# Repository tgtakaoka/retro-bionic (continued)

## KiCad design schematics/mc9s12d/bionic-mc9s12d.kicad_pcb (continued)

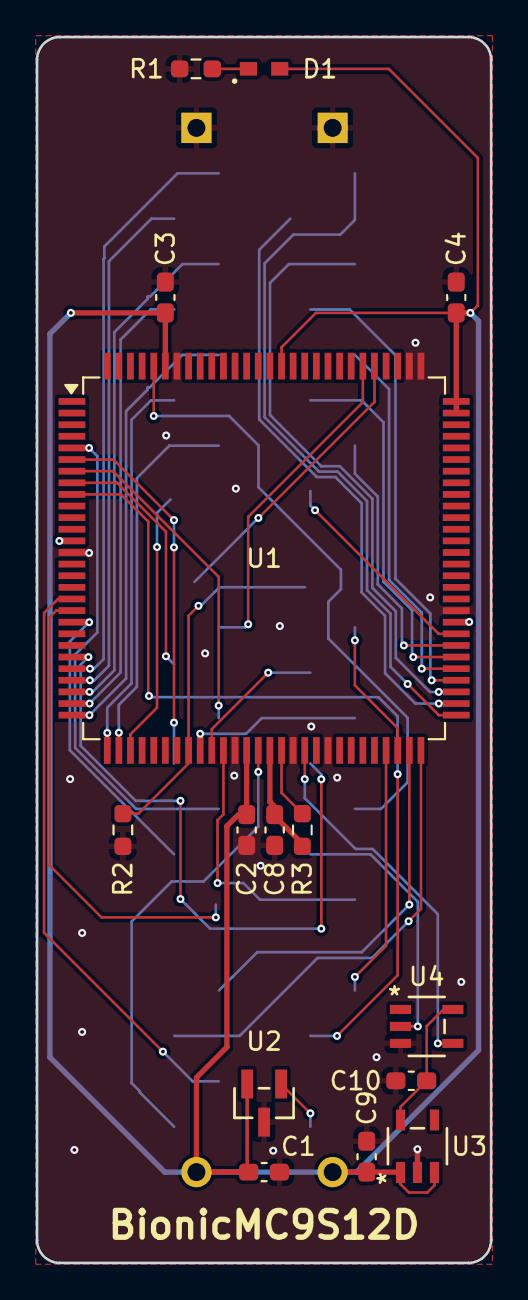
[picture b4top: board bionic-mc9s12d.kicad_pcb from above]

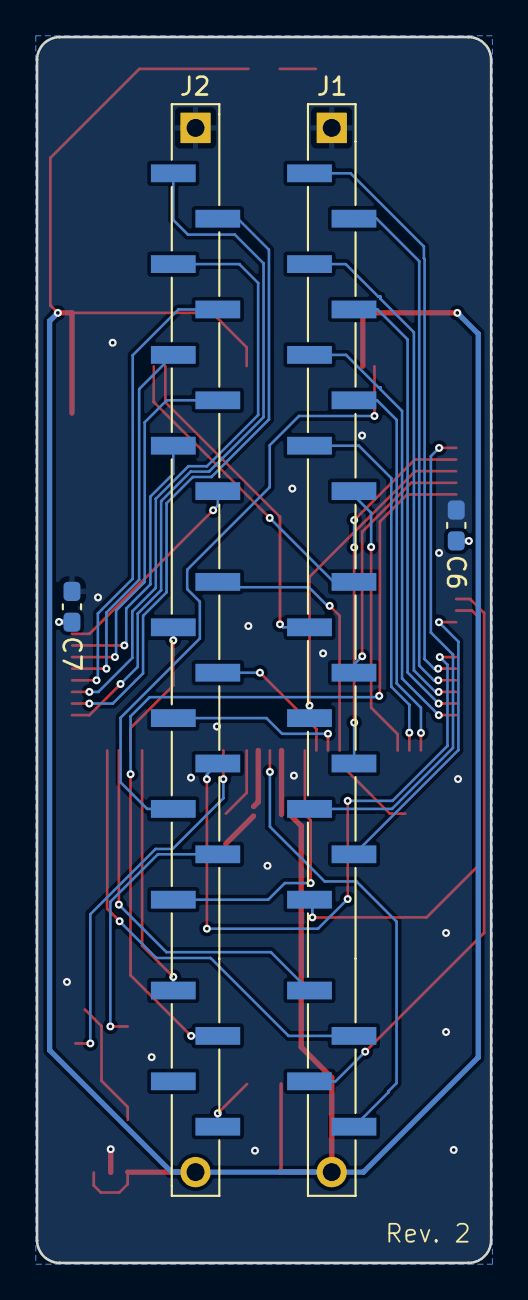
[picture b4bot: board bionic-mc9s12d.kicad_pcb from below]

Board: 2 copper layers, 25.4 x 68.6 mm, 19 parts (4 on the bottom side), 48 nets.

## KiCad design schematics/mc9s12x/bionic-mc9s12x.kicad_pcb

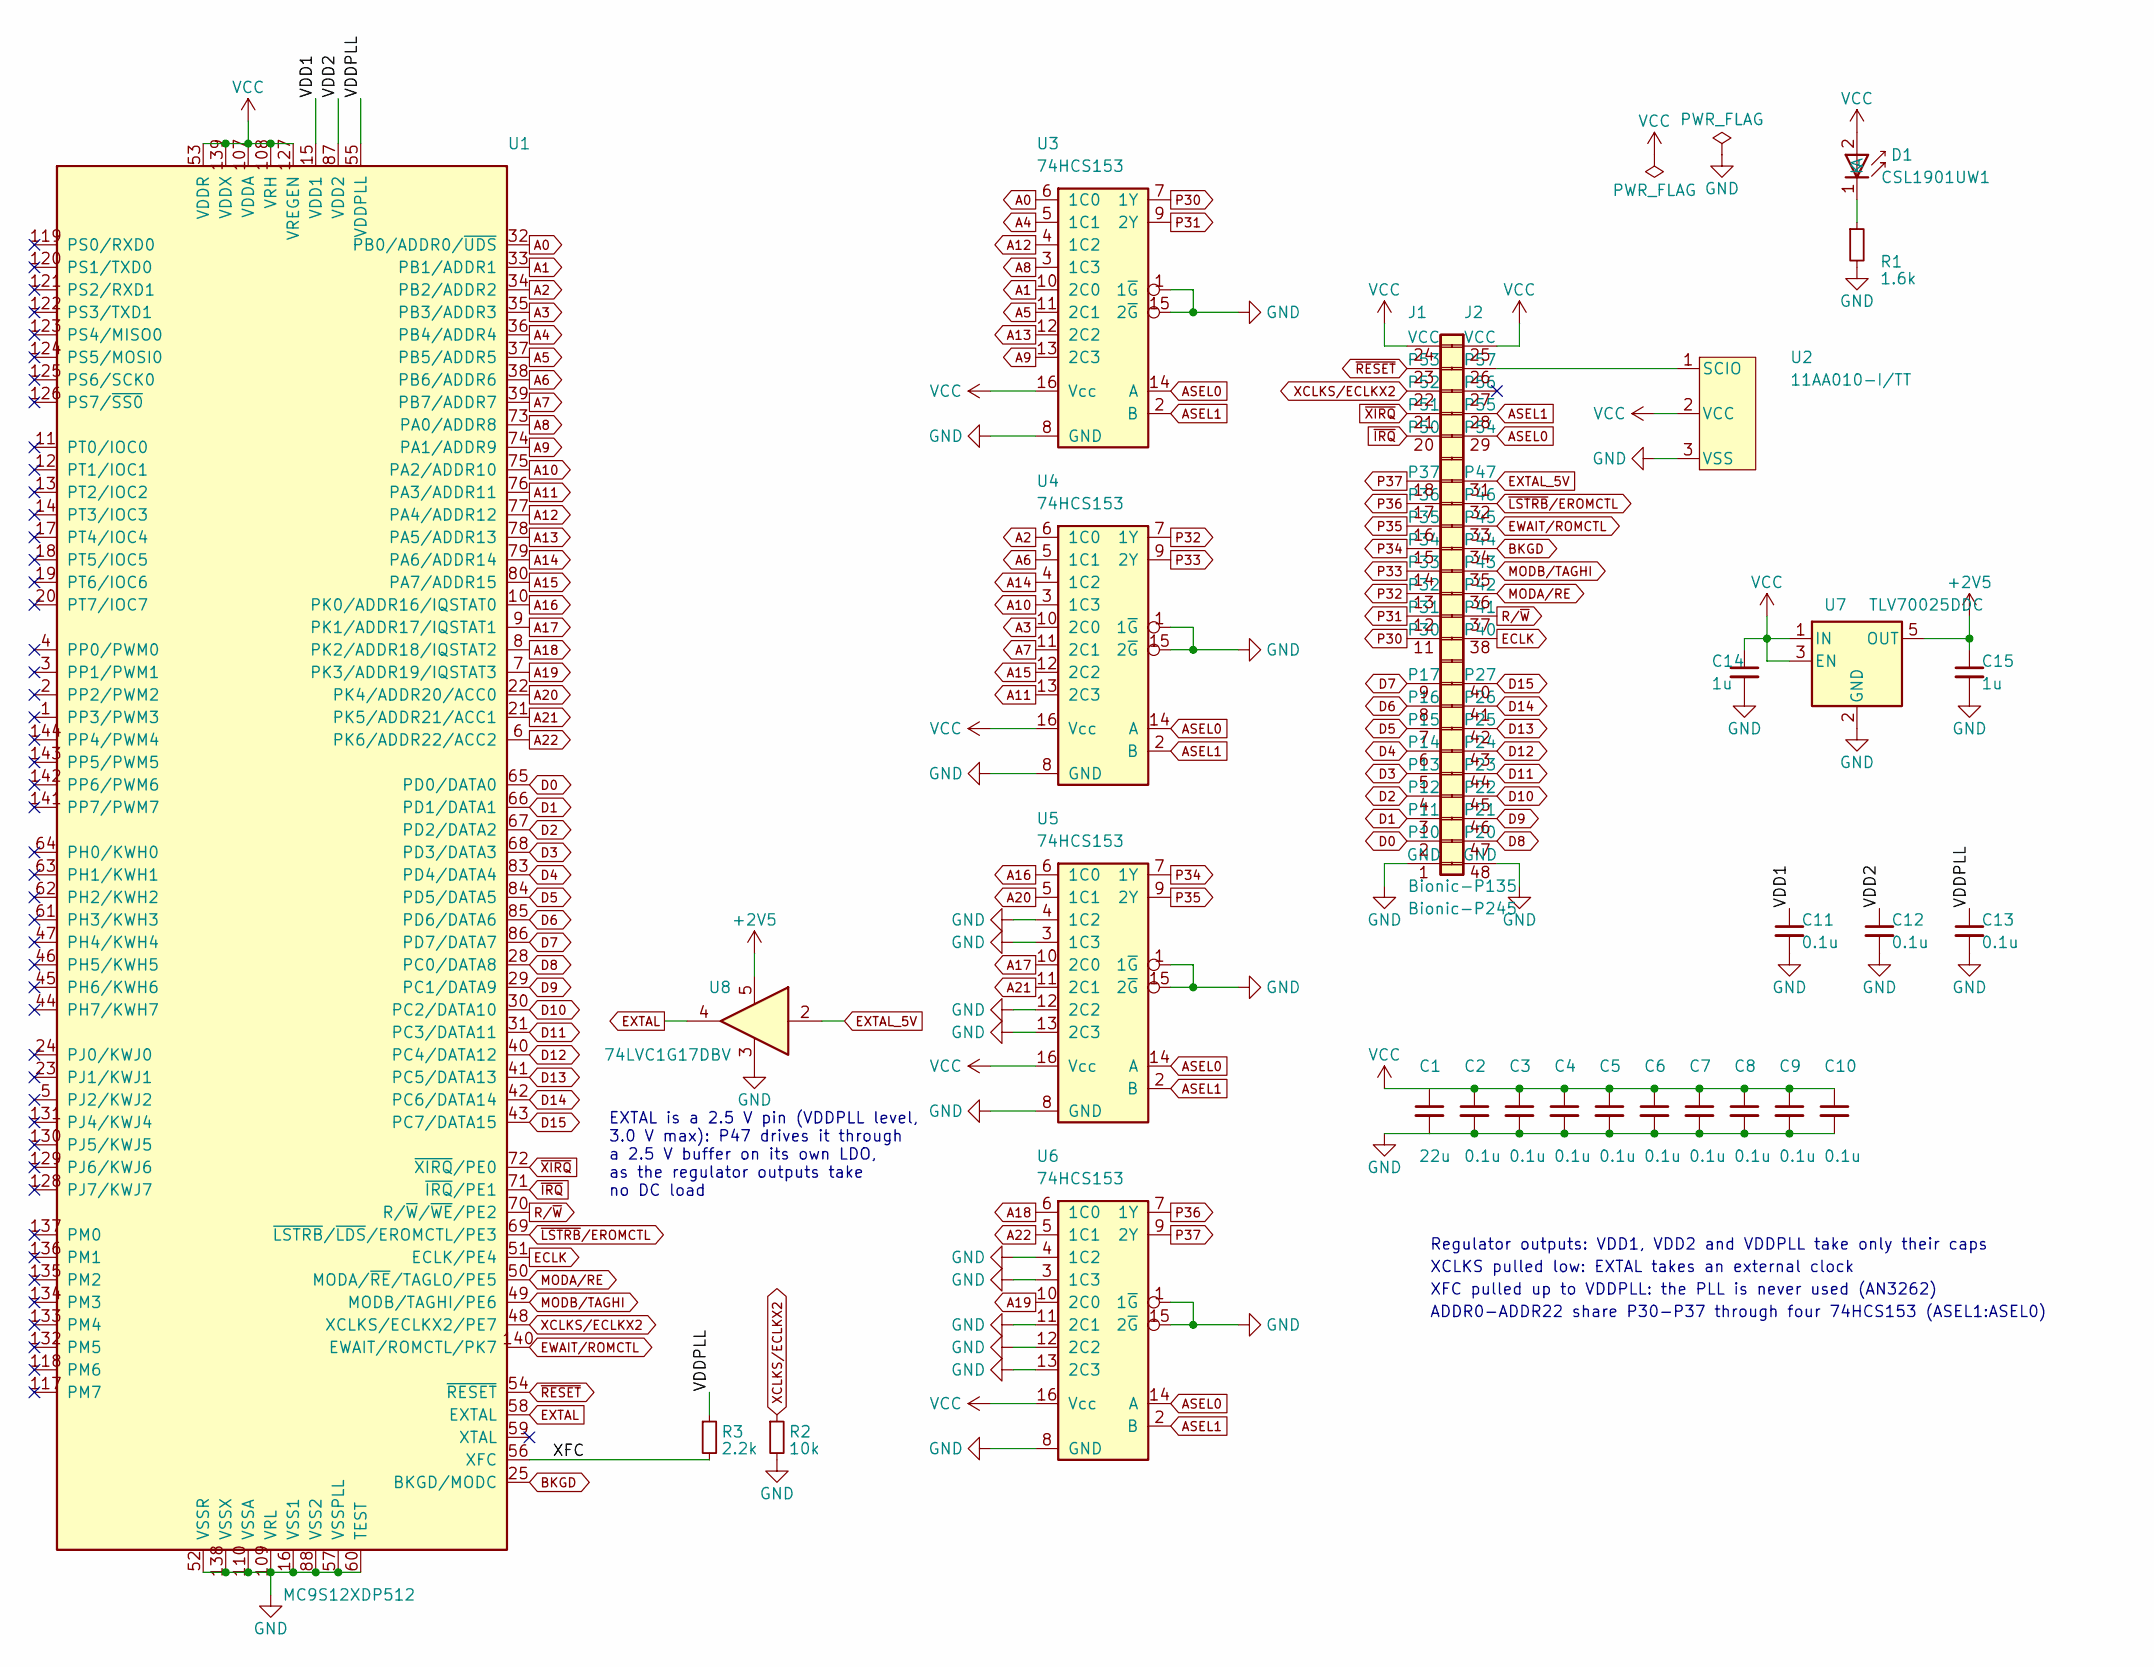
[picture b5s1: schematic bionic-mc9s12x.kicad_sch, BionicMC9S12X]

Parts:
C1: 22u; C_0603_1608Metric_Pad1.08x0.95mm_HandSolder
C2, C3, C4, C5, C6, C7, C8, C9, C10, C11, C12, C13: 0.1u; C_0603_1608Metric_Pad1.08x0.95mm_HandSolder
C14, C15: 1u; C_0603_1608Metric_Pad1.08x0.95mm_HandSolder
D1: CSL1901UW1; LED_CSL1901UW1_ROM-M
J1: Bionic-P135; Bionic-P135_SMT
J2: Bionic-P245; Bionic-P245_SMT
R1: 1.6k; R_0603_1608Metric_Pad0.98x0.95mm_HandSolder
R2: 10k; R_0603_1608Metric_Pad0.98x0.95mm_HandSolder
R3: 2.2k; R_0603_1608Metric_Pad0.98x0.95mm_HandSolder
U1: MC9S12XDP512; LQFP-144_20x20mm_P0.5mm
U2: 11AA010-I/TT; SOT-23_MC_MCH-M
U3, U4, U5, U6: 74HCS153; PW16-M
U7: TLV70025DDC; DBV5-M
U8: 74LVC1G17DBV; DBV5-M

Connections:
+2V5: C15.1, U7.5 (OUT), U8.5 (VCC)
/VDD1: C11.1, U1.15 (VDD1)
/VDD2: C12.1, U1.87 (VDD2)
/VDDPLL: C13.1, R3.1, U1.55 (VDDPLL)
/XFC: R3.2, U1.56 (XFC)
A0: U1.32 (PB0/ADDR0/~UDS), U3.6 (1C0)
A1: U1.33 (PB1/ADDR1), U3.10 (2C0)
A2: U1.34 (PB2/ADDR2), U4.6 (1C0)
A3: U1.35 (PB3/ADDR3), U4.10 (2C0)
A4: U1.36 (PB4/ADDR4), U3.5 (1C1)
A5: U1.37 (PB5/ADDR5), U3.11 (2C1)
A6: U1.38 (PB6/ADDR6), U4.5 (1C1)
A7: U1.39 (PB7/ADDR7), U4.11 (2C1)
A8: U1.73 (PA0/ADDR8), U3.3 (1C3)
A9: U1.74 (PA1/ADDR9), U3.13 (2C3)
A10: U1.75 (PA2/ADDR10), U4.3 (1C3)
A11: U1.76 (PA3/ADDR11), U4.13 (2C3)
A12: U1.77 (PA4/ADDR12), U3.4 (1C2)
A13: U1.78 (PA5/ADDR13), U3.12 (2C2)
A14: U1.79 (PA6/ADDR14), U4.4 (1C2)
A15: U1.80 (PA7/ADDR15), U4.12 (2C2)
A16: U1.10 (PK0/ADDR16/IQSTAT0), U5.6 (1C0)
A17: U1.9 (PK1/ADDR17/IQSTAT1), U5.10 (2C0)
A18: U1.8 (PK2/ADDR18/IQSTAT2), U6.6 (1C0)
A19: U1.7 (PK3/ADDR19/IQSTAT3), U6.10 (2C0)
A20: U1.22 (PK4/ADDR20/ACC0), U5.5 (1C1)
A21: U1.21 (PK5/ADDR21/ACC1), U5.11 (2C1)
A22: U1.6 (PK6/ADDR22/ACC2), U6.5 (1C1)
ASEL0: J2.29 (P54), U3.14 (A), U4.14 (A), U5.14 (A), U6.14 (A)
ASEL1: J2.28 (P55), U3.2 (B), U4.2 (B), U5.2 (B), U6.2 (B)
BKGD: J2.34 (P44), U1.25 (BKGD/MODC)
D0: J1.2 (P10), U1.65 (PD0/DATA0)
D1: J1.3 (P11), U1.66 (PD1/DATA1)
D2: J1.4 (P12), U1.67 (PD2/DATA2)
D3: J1.5 (P13), U1.68 (PD3/DATA3)
D4: J1.6 (P14), U1.83 (PD4/DATA4)
D5: J1.7 (P15), U1.84 (PD5/DATA5)
D6: J1.8 (P16), U1.85 (PD6/DATA6)
D7: J1.9 (P17), U1.86 (PD7/DATA7)
D8: J2.47 (P20), U1.28 (PC0/DATA8)
D9: J2.46 (P21), U1.29 (PC1/DATA9)
D10: J2.45 (P22), U1.30 (PC2/DATA10)
D11: J2.44 (P23), U1.31 (PC3/DATA11)
D12: J2.43 (P24), U1.40 (PC4/DATA12)
D13: J2.42 (P25), U1.41 (PC5/DATA13)
D14: J2.41 (P26), U1.42 (PC6/DATA14)
D15: J2.40 (P27), U1.43 (PC7/DATA15)
ECLK: J2.38 (P40), U1.51 (ECLK/PE4)
EWAIT/ROMCTL: J2.33 (P45), U1.140 (EWAIT/ROMCTL/PK7)
EXTAL: U1.58 (EXTAL), U8.4 (Y)
EXTAL_5V: J2.31 (P47), U8.2 (A)
GND: C1.2, C2.2, C3.2, C4.2, C5.2, C6.2, C7.2, C8.2, C9.2, C10.2, C11.2, C12.2, C13.2, C14.2, C15.2, J1.1 (GND), J2.48 (GND), R1.2, R2.2, U1.16 (VSS1), U1.27 (VSSX), U1.52 (VSSR), U1.57 (VSSPLL), U1.60 (TEST), U1.81 (VSSR), U1.88 (VSS2), U1.109 (VRL), U1.110 (VSSA), U1.138 (VSSX), U2.3 (VSS), U3.1 (1~G), U3.8 (GND), U3.15 (2~G), U4.1 (1~G), U4.8 (GND), U4.15 (2~G), U5.1 (1~G), U5.3 (1C3), U5.4 (1C2), U5.8 (GND), U5.12 (2C2), U5.13 (2C3), U5.15 (2~G), U6.1 (1~G), U6.3 (1C3), U6.4 (1C2), U6.8 (GND), U6.11 (2C1), U6.12 (2C2), U6.13 (2C3), U6.15 (2~G), U7.2 (GND), U8.3 (GND)
MODA/RE: J2.36 (P42), U1.50 (MODA/~RE/TAGLO/PE5)
MODB/TAGHI: J2.35 (P43), U1.49 (MODB/TAGHI/PE6)
unnamed: D1.1 (K), R1.1
unnamed: J2.26 (P57), U2.1 (SCIO)
P30: J1.11 (P30), U3.7 (1Y)
P31: J1.12 (P31), U3.9 (2Y)
P32: J1.13 (P32), U4.7 (1Y)
P33: J1.14 (P33), U4.9 (2Y)
P34: J1.15 (P34), U5.7 (1Y)
P35: J1.16 (P35), U5.9 (2Y)
P36: J1.17 (P36), U6.7 (1Y)
P37: J1.18 (P37), U6.9 (2Y)
R/~W: J2.37 (P41), U1.70 (R/~W/~WE/PE2)
VCC: C1.1, C2.1, C3.1, C4.1, C5.1, C6.1, C7.1, C8.1, C9.1, C10.1, C14.1, D1.2 (A), J1.24 (VCC), J2.25 (VCC), U1.26 (VDDX), U1.53 (VDDR), U1.82 (VDDR), U1.107 (VDDA), U1.108 (VRH), U1.127 (VREGEN), U1.139 (VDDX), U2.2 (VCC), U3.16 (Vcc), U4.16 (Vcc), U5.16 (Vcc), U6.16 (Vcc), U7.1 (IN), U7.3 (EN)
XCLKS/ECLKX2: J1.22 (P52), R2.1, U1.48 (XCLKS/ECLKX2/PE7)
~IRQ: J1.20 (P50), U1.71 (~IRQ/PE1)
~LSTRB/EROMCTL: J2.32 (P46), U1.69 (~LSTRB/~LDS/EROMCTL/PE3)
~RESET: J1.23 (P53), U1.54 (~RESET)
~XIRQ: J1.21 (P51), U1.72 (~XIRQ/PE0)

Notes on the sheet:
XCLKS pulled low: EXTAL takes an external clock
ADDR0-ADDR22 share P30-P37 through four 74HCS153 (ASEL1:ASEL0)
XFC pulled up to VDDPLL: the PLL is never used (AN3262)
EXTAL is a 2.5 V pin (VDDPLL level, 3.0 V max): P47 drives it through a 2.5 V buffer on its own LDO, as the regulator outputs take no DC load
Regulator outputs: VDD1, VDD2 and VDDPLL take only their caps

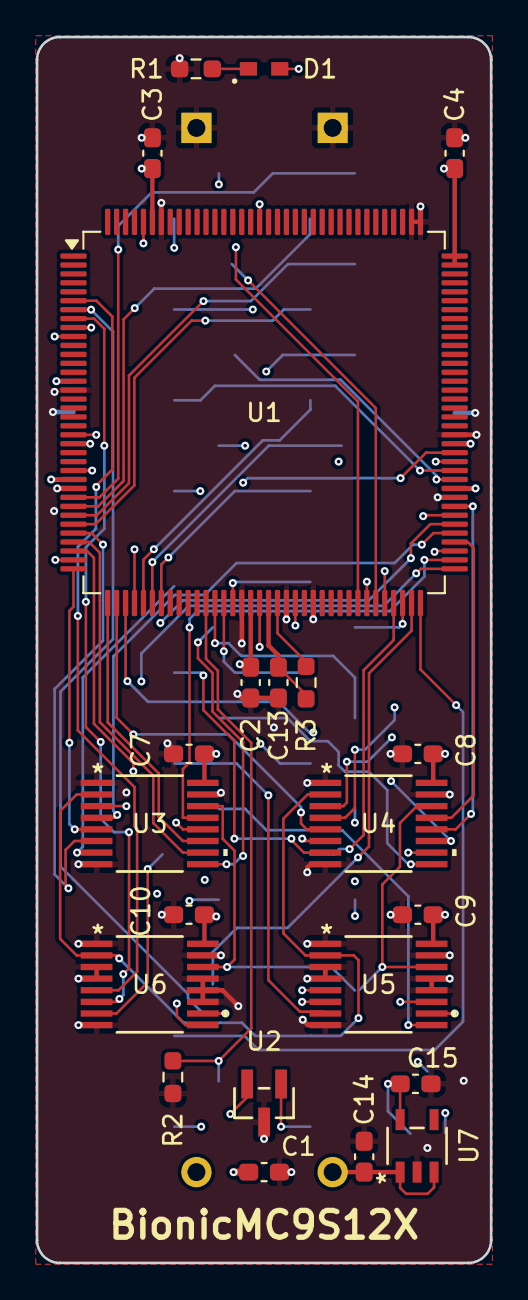
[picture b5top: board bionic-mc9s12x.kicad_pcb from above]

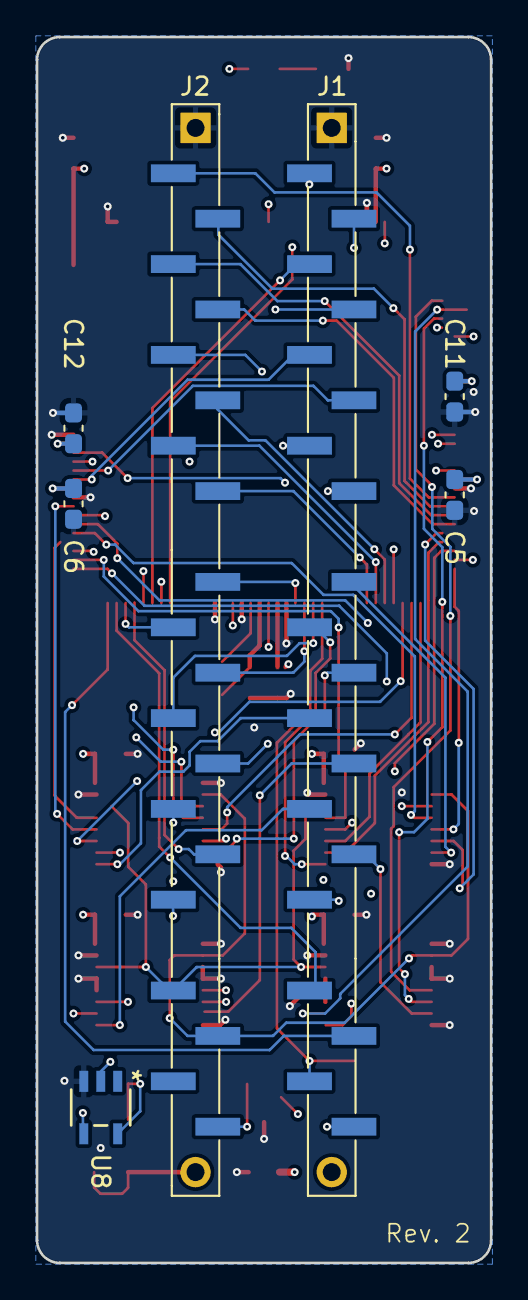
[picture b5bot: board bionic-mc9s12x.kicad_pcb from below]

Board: 4 copper layers, 25.4 x 68.6 mm, 29 parts (7 on the bottom side), 71 nets.

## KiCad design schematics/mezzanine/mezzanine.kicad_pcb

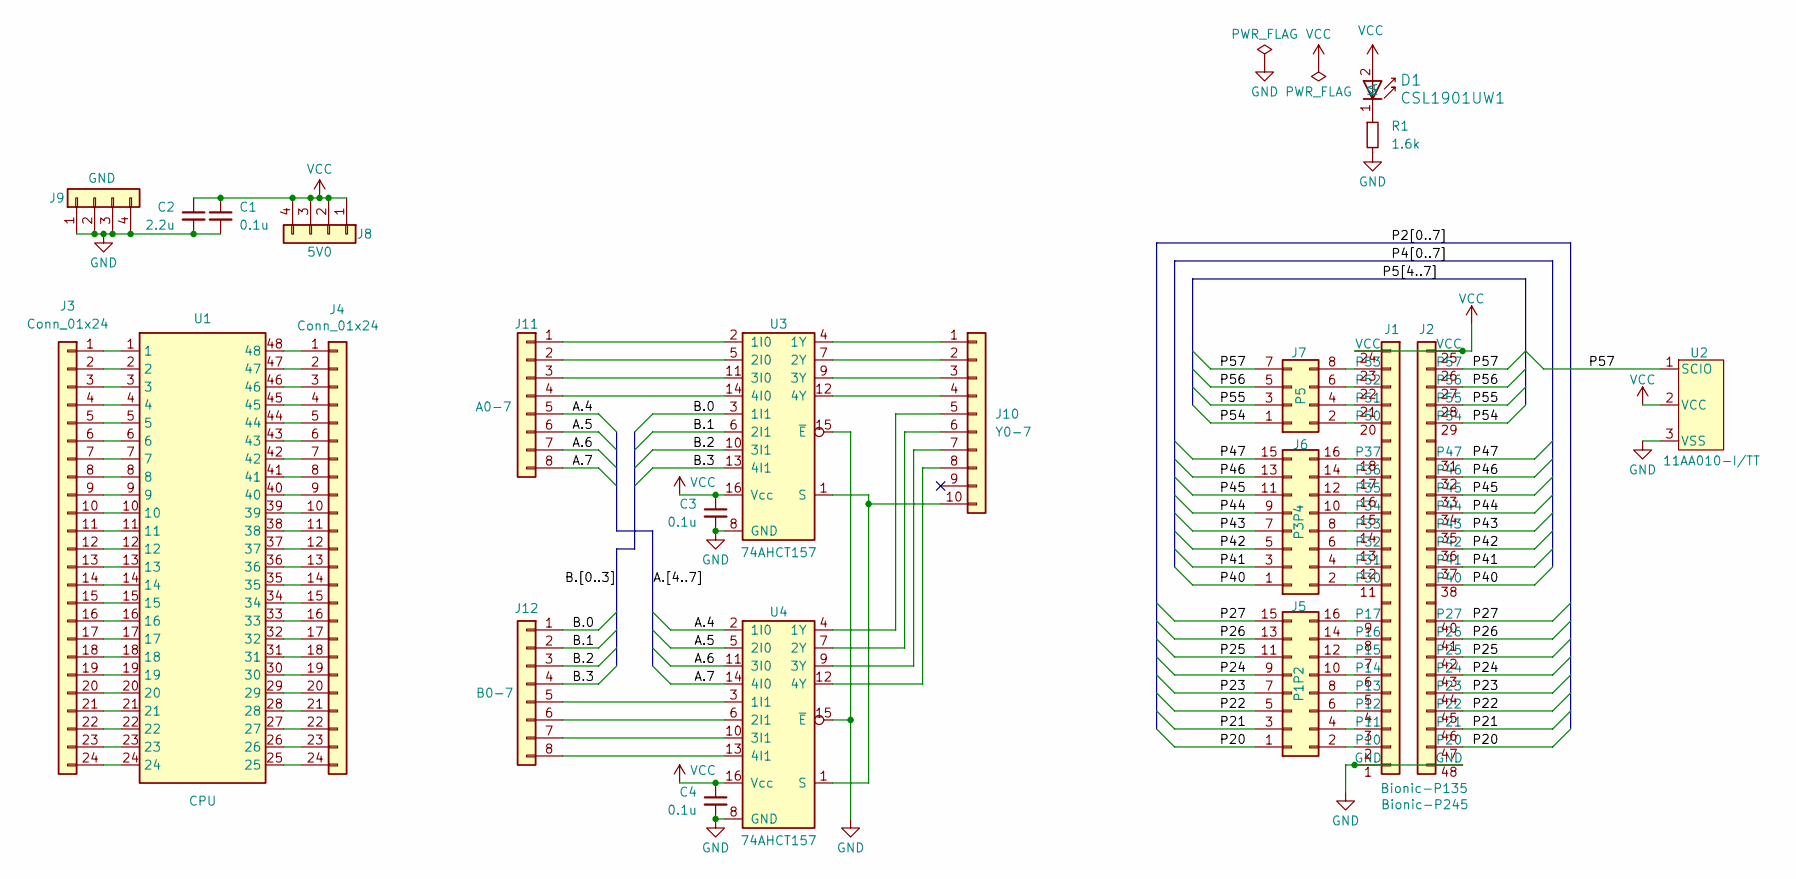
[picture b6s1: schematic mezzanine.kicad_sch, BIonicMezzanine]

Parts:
C1, C3, C4: 0.1u; C_0603_1608Metric_Pad1.08x0.95mm_HandSolder
C2: 2.2u; C_0603_1608Metric_Pad1.08x0.95mm_HandSolder
D1: CSL1901UW1; LED_CSL1901UW1_ROM-M
J1: Bionic-P135; Bionic-P135_THT
J2: Bionic-P245; Bionic-P245_THT
J3, J4: Conn_01x24; PinSocket_1x24_P2.54mm_Vertical
J5: P1P2; PinSocket_2x08_P2.54mm_Vertical
J6: P3P4; PinSocket_2x08_P2.54mm_Vertical
J7: P5; PinSocket_2x04_P2.54mm_Vertical
J8: 5V0; PinSocket_1x04_P2.54mm_Vertical
J9: GND; PinSocket_1x04_P2.54mm_Vertical
J10: Y0-7; PinSocket_1x10_P2.54mm_Vertical
J11: A0-7; PinSocket_1x08_P2.54mm_Vertical
J12: B0-7; PinSocket_1x08_P2.54mm_Vertical
R1: 1.6k; R_0603_1608Metric_Pad0.98x0.95mm_HandSolder
U1: CPU; Aries_ZIF_socket_DIP-48-pin
U2: 11AA010-I/TT; SOT-23_MC_MCH-M
U3, U4: 74AHCT157; PW16-M

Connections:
/A.4: J11.5, U4.2 (1I0)
/A.5: J11.6, U4.5 (2I0)
/A.6: J11.7, U4.11 (3I0)
/A.7: J11.8, U4.14 (4I0)
/B.0: J12.1, U3.3 (1I1)
/B.1: J12.2, U3.6 (2I1)
/B.2: J12.3, U3.10 (3I1)
/B.3: J12.4, U3.13 (4I1)
/P20: J2.47 (P20), J5.1
/P21: J2.46 (P21), J5.3
/P22: J2.45 (P22), J5.5
/P23: J2.44 (P23), J5.7
/P24: J2.43 (P24), J5.9
/P25: J2.42 (P25), J5.11
/P26: J2.41 (P26), J5.13
/P27: J2.40 (P27), J5.15
/P40: J2.38 (P40), J6.1
/P41: J2.37 (P41), J6.3
/P42: J2.36 (P42), J6.5
/P43: J2.35 (P43), J6.7
/P44: J2.34 (P44), J6.9
/P45: J2.33 (P45), J6.11
/P46: J2.32 (P46), J6.13
/P47: J2.31 (P47), J6.15
/P54: J2.29 (P54), J7.1
/P55: J2.28 (P55), J7.3
/P56: J2.27 (P56), J7.5
/P57: J2.26 (P57), J7.7, U2.1 (SCIO)
GND: C1.2, C2.2, C3.2, C4.2, J1.1 (GND), J2.48 (GND), J9.1, J9.2, J9.3, J9.4, R1.2, U2.3 (VSS), U3.8 (GND), U3.15 (~E), U4.8 (GND), U4.15 (~E)
unnamed: D1.1 (K), R1.1
unnamed: J1.2 (P10), J5.2
unnamed: J1.3 (P11), J5.4
unnamed: J1.4 (P12), J5.6
unnamed: J1.5 (P13), J5.8
unnamed: J1.6 (P14), J5.10
unnamed: J1.7 (P15), J5.12
unnamed: J1.8 (P16), J5.14
unnamed: J1.9 (P17), J5.16
unnamed: J1.11 (P30), J6.2
unnamed: J1.12 (P31), J6.4
unnamed: J1.13 (P32), J6.6
unnamed: J1.14 (P33), J6.8
unnamed: J1.15 (P34), J6.10
unnamed: J1.16 (P35), J6.12
unnamed: J1.17 (P36), J6.14
unnamed: J1.18 (P37), J6.16
unnamed: J1.20 (P50), J7.2
unnamed: J1.21 (P51), J7.4
unnamed: J1.22 (P52), J7.6
unnamed: J1.23 (P53), J7.8
unnamed: J3.1, U1.1
unnamed: J3.2, U1.2
unnamed: J3.3, U1.3
unnamed: J3.4, U1.4
unnamed: J3.5, U1.5
unnamed: J3.6, U1.6
unnamed: J3.7, U1.7
unnamed: J3.8, U1.8
unnamed: J3.9, U1.9
unnamed: J3.10, U1.10
unnamed: J3.11, U1.11
unnamed: J3.12, U1.12
unnamed: J3.13, U1.13
unnamed: J3.14, U1.14
unnamed: J3.15, U1.15
unnamed: J3.16, U1.16
unnamed: J3.17, U1.17
unnamed: J3.18, U1.18
unnamed: J3.19, U1.19
unnamed: J3.20, U1.20
unnamed: J3.21, U1.21
unnamed: J3.22, U1.22
unnamed: J3.23, U1.23
unnamed: J3.24, U1.24
unnamed: J4.1, U1.48
unnamed: J4.2, U1.47
unnamed: J4.3, U1.46
unnamed: J4.4, U1.45
unnamed: J4.5, U1.44
unnamed: J4.6, U1.43
unnamed: J4.7, U1.42
unnamed: J4.8, U1.41
unnamed: J4.9, U1.40
unnamed: J4.10, U1.39
unnamed: J4.11, U1.38
unnamed: J4.12, U1.37
unnamed: J4.13, U1.36
unnamed: J4.14, U1.35
unnamed: J4.15, U1.34
unnamed: J4.16, U1.33
unnamed: J4.17, U1.32
unnamed: J4.18, U1.31
unnamed: J4.19, U1.30
unnamed: J4.20, U1.29
unnamed: J4.21, U1.28
unnamed: J4.22, U1.27
unnamed: J4.23, U1.26
unnamed: J4.24, U1.25
unnamed: J10.1, U3.4 (1Y)
unnamed: J10.2, U3.7 (2Y)
unnamed: J10.3, U3.9 (3Y)
unnamed: J10.4, U3.12 (4Y)
unnamed: J10.5, U4.4 (1Y)
unnamed: J10.6, U4.7 (2Y)
unnamed: J10.7, U4.9 (3Y)
unnamed: J10.8, U4.12 (4Y)
unnamed: J10.10, U3.1 (S), U4.1 (S)
unnamed: J11.1, U3.2 (1I0)
unnamed: J11.2, U3.5 (2I0)
unnamed: J11.3, U3.11 (3I0)
unnamed: J11.4, U3.14 (4I0)
unnamed: J12.5, U4.3 (1I1)
unnamed: J12.6, U4.6 (2I1)
unnamed: J12.7, U4.10 (3I1)
unnamed: J12.8, U4.13 (4I1)
VCC: C1.1, C2.1, C3.1, C4.1, D1.2 (A), J1.24 (VCC), J2.25 (VCC), J8.1, J8.2, J8.3, J8.4, U2.2 (VCC), U3.16 (Vcc), U4.16 (Vcc)

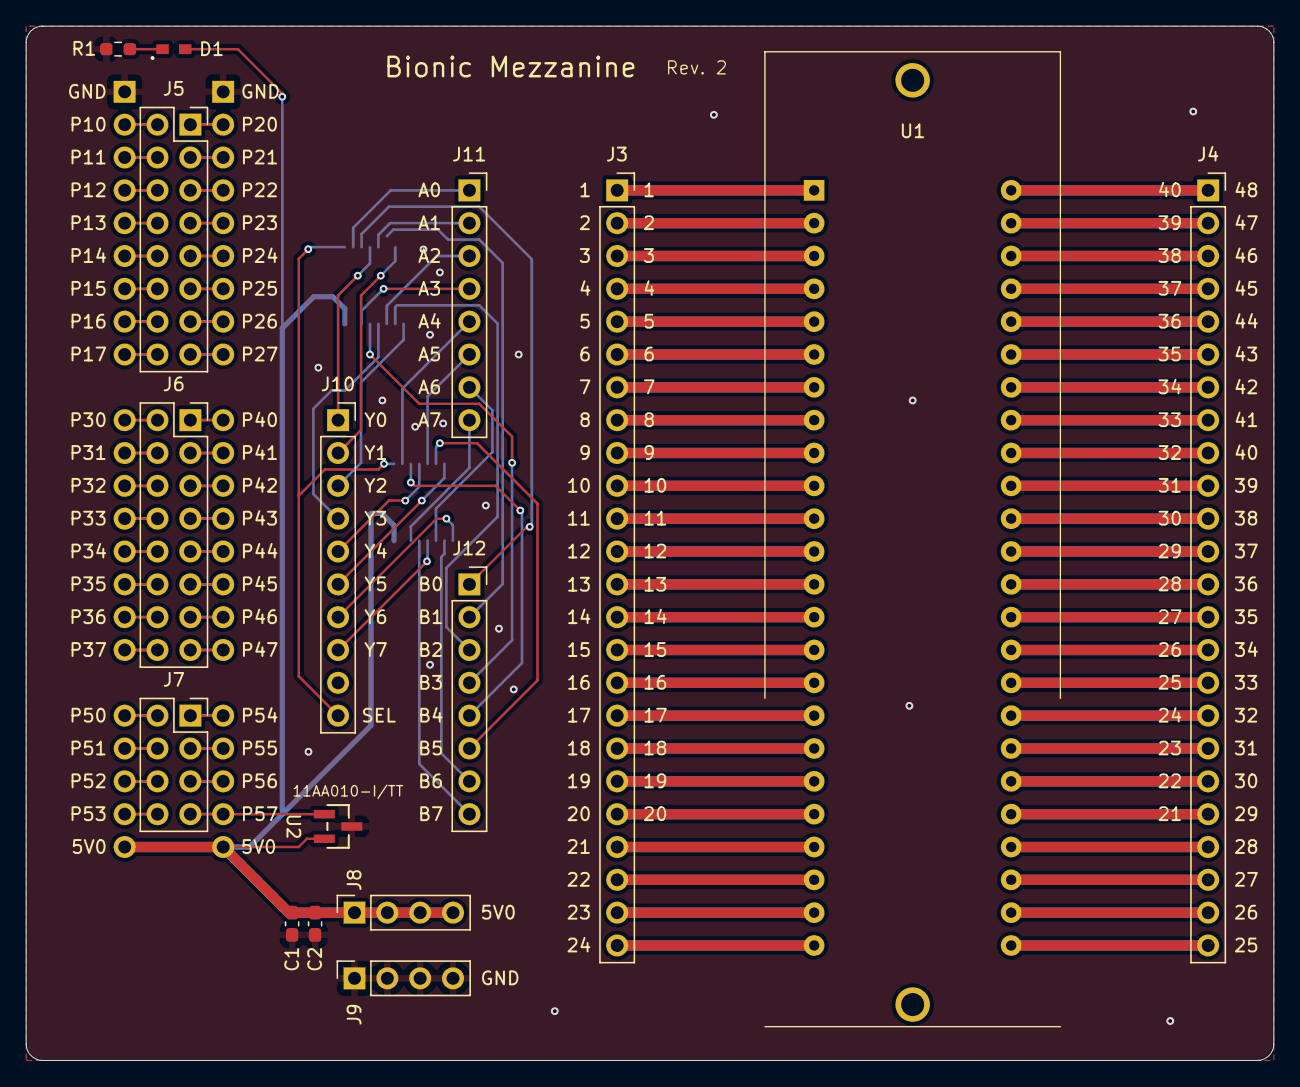
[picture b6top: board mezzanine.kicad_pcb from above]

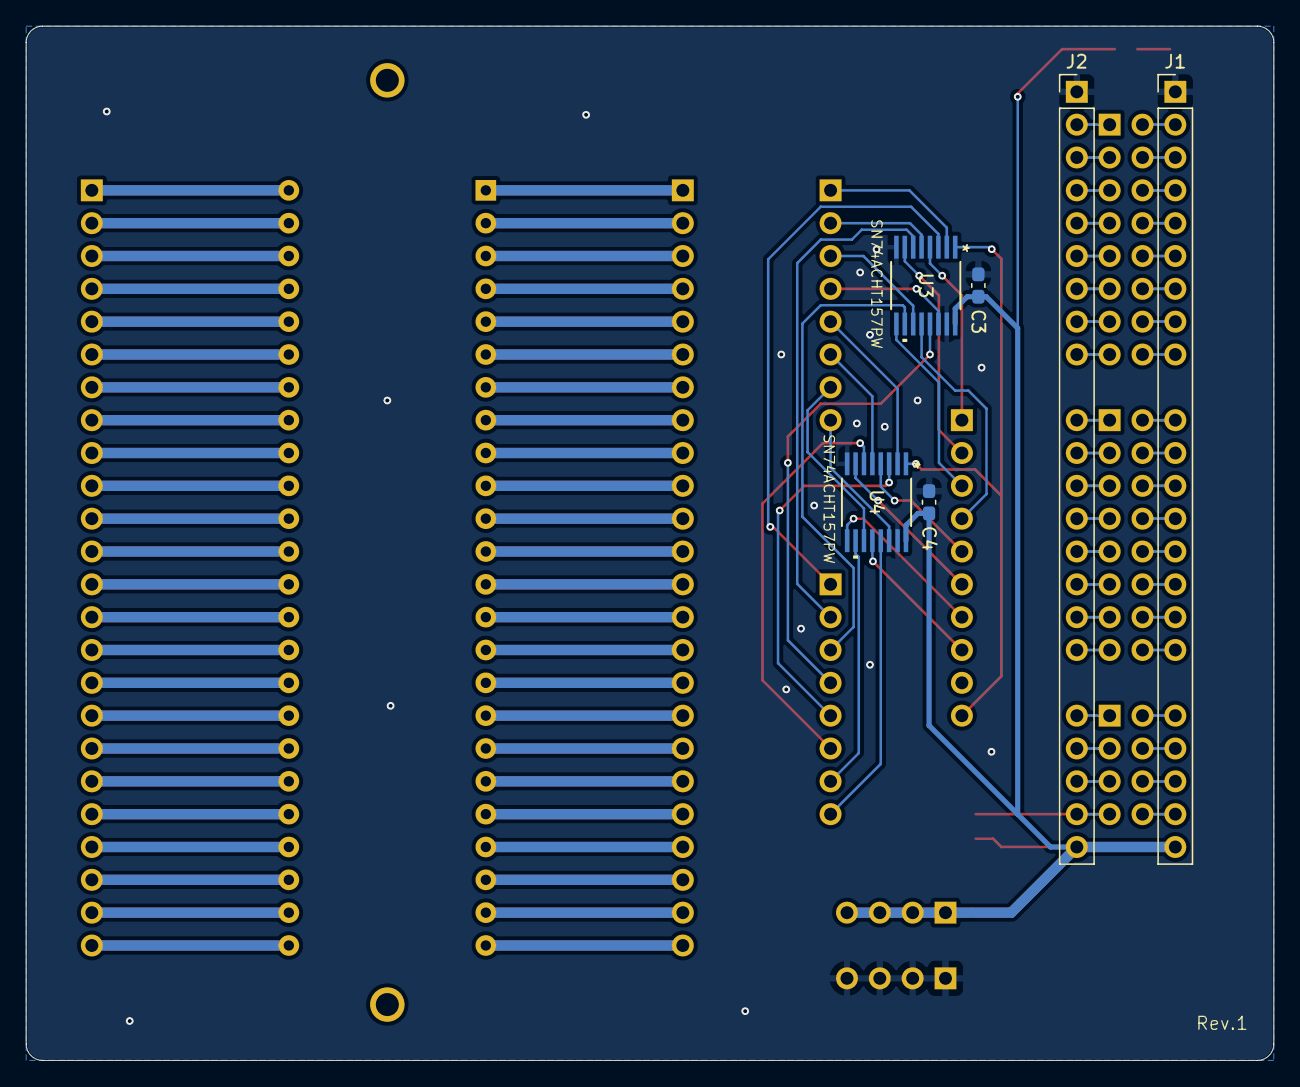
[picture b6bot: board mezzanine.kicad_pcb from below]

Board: 2 copper layers, 96.5 x 80.0 mm, 22 parts (6 on the bottom side), 116 nets.

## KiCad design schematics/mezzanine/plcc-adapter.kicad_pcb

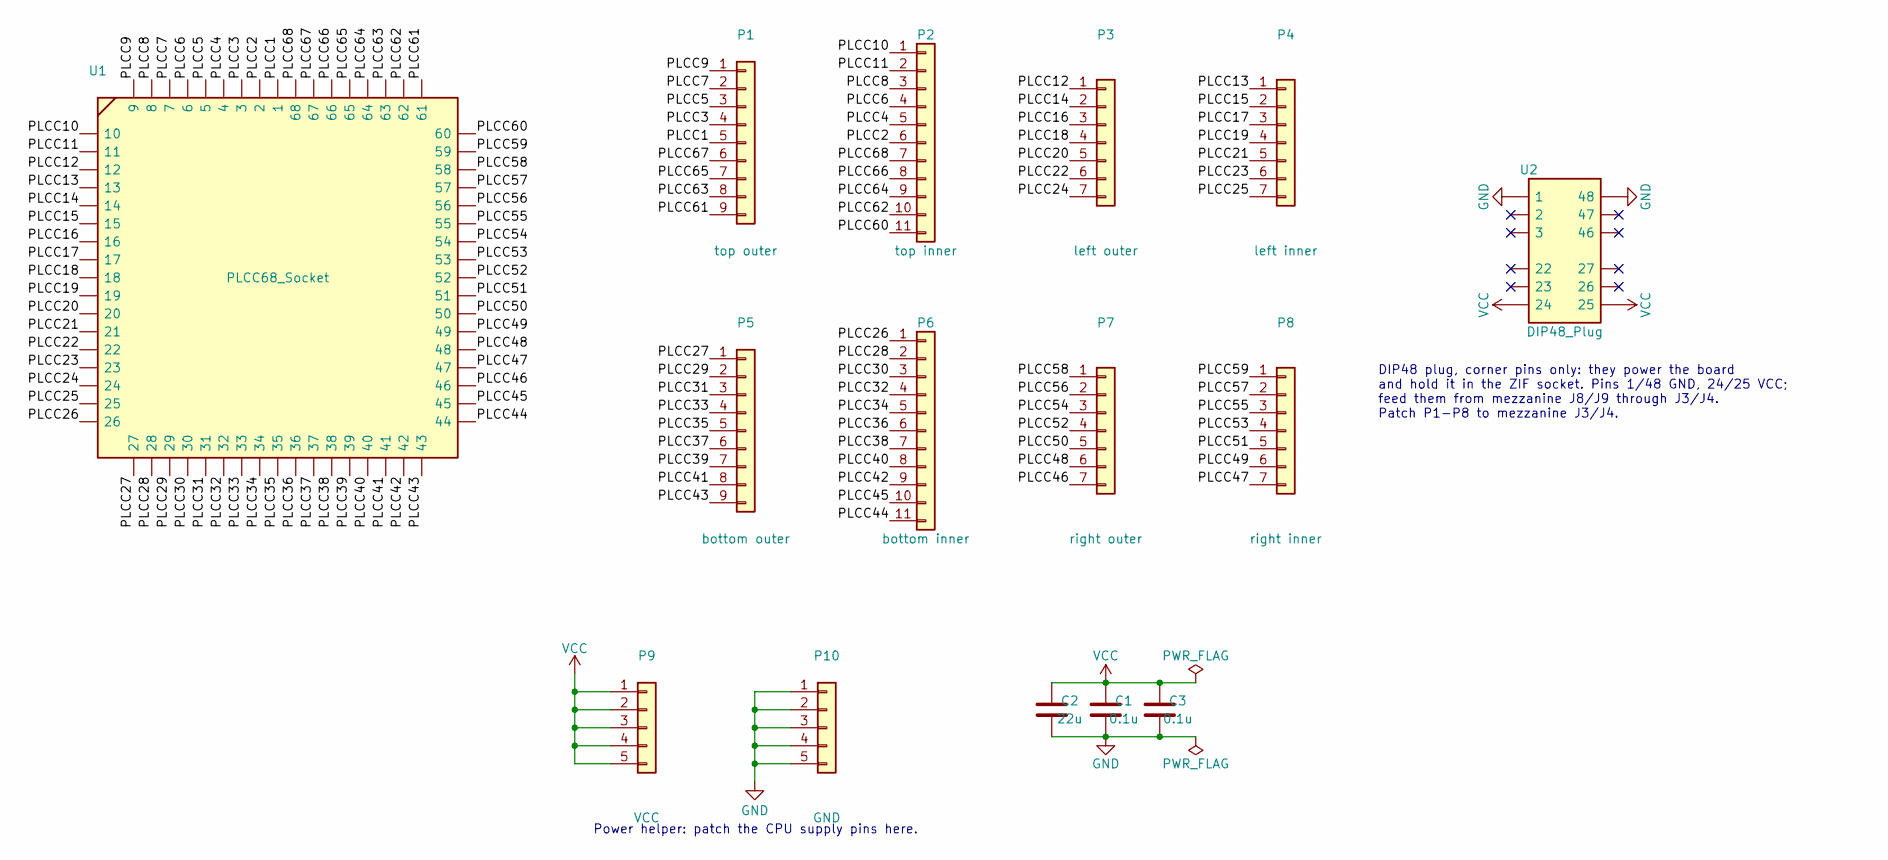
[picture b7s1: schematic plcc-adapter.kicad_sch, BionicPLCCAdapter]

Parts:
C1, C3: 0.1u; C_0603_1608Metric_Pad1.08x0.95mm_HandSolder
C2: 22u; C_0603_1608Metric_Pad1.08x0.95mm_HandSolder
P1: top outer; PinSocket_1x09_P2.54mm_Vertical_Oval
P2: top inner; PinSocket_1x11_P2.54mm_Vertical_Oval
P3: left outer; PinSocket_1x07_P2.54mm_Vertical_Oval
P4: left inner; PinSocket_1x07_P2.54mm_Vertical_Oval
P5: bottom outer; PinSocket_1x09_P2.54mm_Vertical_Oval
P6: bottom inner; PinSocket_1x11_P2.54mm_Vertical_Oval
P7: right outer; PinSocket_1x07_P2.54mm_Vertical_Oval
P8: right inner; PinSocket_1x07_P2.54mm_Vertical_Oval
P9: VCC; PinSocket_1x05_P2.54mm_Vertical_Oval
P10: GND; PinSocket_1x05_P2.54mm_Vertical_Oval
U1: PLCC68_Socket; PLCC-68_THT-Socket_Akizuki
U2: DIP48_Plug

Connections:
/PLCC1: P1.5, U1.1
/PLCC2: P2.6, U1.2
/PLCC3: P1.4, U1.3
/PLCC4: P2.5, U1.4
/PLCC5: P1.3, U1.5
/PLCC6: P2.4, U1.6
/PLCC7: P1.2, U1.7
/PLCC8: P2.3, U1.8
/PLCC9: P1.1, U1.9
/PLCC10: P2.1, U1.10
/PLCC11: P2.2, U1.11
/PLCC12: P3.1, U1.12
/PLCC13: P4.1, U1.13
/PLCC14: P3.2, U1.14
/PLCC15: P4.2, U1.15
/PLCC16: P3.3, U1.16
/PLCC17: P4.3, U1.17
/PLCC18: P3.4, U1.18
/PLCC19: P4.4, U1.19
/PLCC20: P3.5, U1.20
/PLCC21: P4.5, U1.21
/PLCC22: P3.6, U1.22
/PLCC23: P4.6, U1.23
/PLCC24: P3.7, U1.24
/PLCC25: P4.7, U1.25
/PLCC26: P6.1, U1.26
/PLCC27: P5.1, U1.27
/PLCC28: P6.2, U1.28
/PLCC29: P5.2, U1.29
/PLCC30: P6.3, U1.30
/PLCC31: P5.3, U1.31
/PLCC32: P6.4, U1.32
/PLCC33: P5.4, U1.33
/PLCC34: P6.5, U1.34
/PLCC35: P5.5, U1.35
/PLCC36: P6.6, U1.36
/PLCC37: P5.6, U1.37
/PLCC38: P6.7, U1.38
/PLCC39: P5.7, U1.39
/PLCC40: P6.8, U1.40
/PLCC41: P5.8, U1.41
/PLCC42: P6.9, U1.42
/PLCC43: P5.9, U1.43
/PLCC44: P6.11, U1.44
/PLCC45: P6.10, U1.45
/PLCC46: P7.7, U1.46
/PLCC47: P8.7, U1.47
/PLCC48: P7.6, U1.48
/PLCC49: P8.6, U1.49
/PLCC50: P7.5, U1.50
/PLCC51: P8.5, U1.51
/PLCC52: P7.4, U1.52
/PLCC53: P8.4, U1.53
/PLCC54: P7.3, U1.54
/PLCC55: P8.3, U1.55
/PLCC56: P7.2, U1.56
/PLCC57: P8.2, U1.57
/PLCC58: P7.1, U1.58
/PLCC59: P8.1, U1.59
/PLCC60: P2.11, U1.60
/PLCC61: P1.9, U1.61
/PLCC62: P2.10, U1.62
/PLCC63: P1.8, U1.63
/PLCC64: P2.9, U1.64
/PLCC65: P1.7, U1.65
/PLCC66: P2.8, U1.66
/PLCC67: P1.6, U1.67
/PLCC68: P2.7, U1.68
GND: C1.2, C2.2, C3.2, P10.1, P10.2, P10.3, P10.4, P10.5, U2.1, U2.48
VCC: C1.1, C2.1, C3.1, P9.1, P9.2, P9.3, P9.4, P9.5, U2.24, U2.25

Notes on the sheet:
DIP48 plug, corner pins only: they power the board and hold it in the ZIF socket. Pins 1/48 GND, 24/25 VCC; feed them from mezzanine J8/J9 through J3/J4. Patch P1-P8 to mezzanine J3/J4.
Power helper: patch the CPU supply pins here.

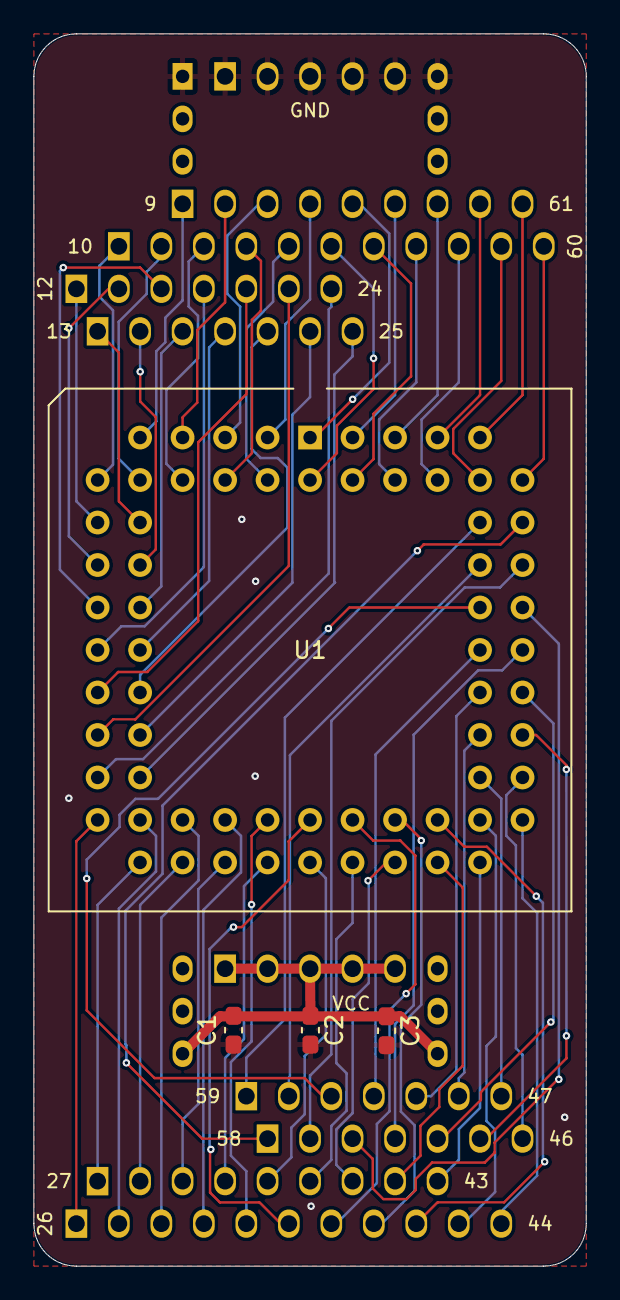
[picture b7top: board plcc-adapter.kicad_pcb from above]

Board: 2 copper layers, 33.0 x 73.7 mm, 15 parts (0 on the bottom side), 70 nets.

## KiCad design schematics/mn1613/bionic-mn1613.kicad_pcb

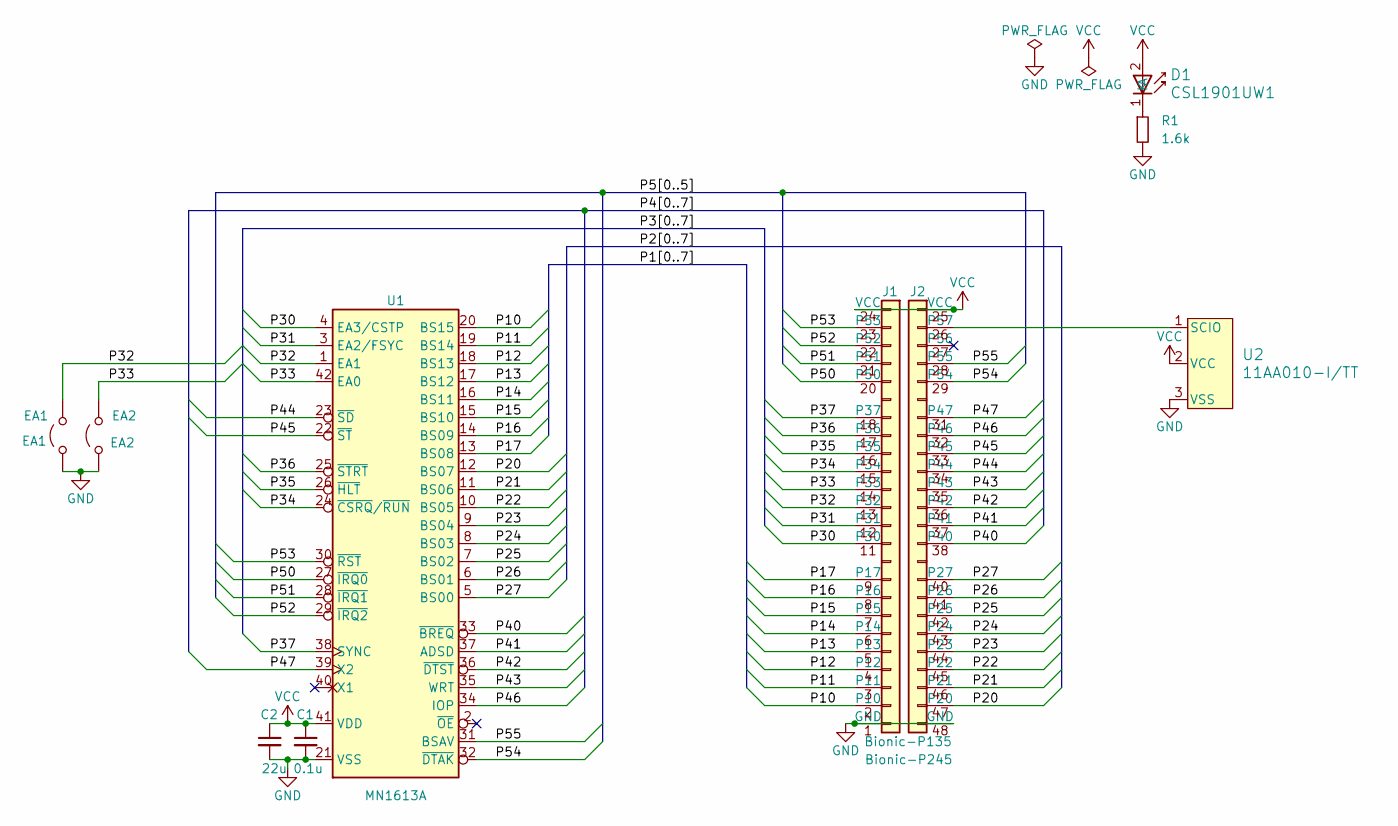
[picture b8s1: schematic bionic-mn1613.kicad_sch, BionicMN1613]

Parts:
C1: 0.1u; C_0603_1608Metric_Pad1.08x0.95mm_HandSolder
C2: 22u; C_0603_1608Metric_Pad1.08x0.95mm_HandSolder
D1: CSL1901UW1; LED_CSL1901UW1_ROM-M
EA1: EA1; SolderJumper-2_P1.3mm_Open_RoundedPad1.0x1.5mm
EA2: EA2; SolderJumper-2_P1.3mm_Open_RoundedPad1.0x1.5mm
J1: Bionic-P135; Bionic-P135_THT
J2: Bionic-P245; Bionic-P245_THT
R1: 1.6k; R_0603_1608Metric_Pad0.98x0.95mm_HandSolder
U1: MN1613A; DIP-42_W15.24mm_Socket
U2: 11AA010-I/TT; SOT-23_MC_MCH-M

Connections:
/P10: J1.2 (P10), U1.20 (BS15)
/P11: J1.3 (P11), U1.19 (BS14)
/P12: J1.4 (P12), U1.18 (BS13)
/P13: J1.5 (P13), U1.17 (BS12)
/P14: J1.6 (P14), U1.16 (BS11)
/P15: J1.7 (P15), U1.15 (BS10)
/P16: J1.8 (P16), U1.14 (BS09)
/P17: J1.9 (P17), U1.13 (BS08)
/P20: J2.47 (P20), U1.12 (BS07)
/P21: J2.46 (P21), U1.11 (BS06)
/P22: J2.45 (P22), U1.10 (BS05)
/P23: J2.44 (P23), U1.9 (BS04)
/P24: J2.43 (P24), U1.8 (BS03)
/P25: J2.42 (P25), U1.7 (BS02)
/P26: J2.41 (P26), U1.6 (BS01)
/P27: J2.40 (P27), U1.5 (BS00)
/P30: J1.11 (P30), U1.4 (EA3/CSTP)
/P31: J1.12 (P31), U1.3 (EA2/FSYC)
/P32: EA1.2 (B), J1.13 (P32), U1.1 (EA1)
/P33: EA2.2 (B), J1.14 (P33), U1.42 (EA0)
/P34: J1.15 (P34), U1.24 (~CSRQ/~RUN)
/P35: J1.16 (P35), U1.26 (~HLT)
/P36: J1.17 (P36), U1.25 (~STRT)
/P37: J1.18 (P37), U1.38 (SYNC)
/P40: J2.38 (P40), U1.33 (~BREQ)
/P41: J2.37 (P41), U1.37 (ADSD)
/P42: J2.36 (P42), U1.36 (~DTST)
/P43: J2.35 (P43), U1.35 (WRT)
/P44: J2.34 (P44), U1.23 (~SD)
/P45: J2.33 (P45), U1.22 (~ST)
/P46: J2.32 (P46), U1.34 (IOP)
/P47: J2.31 (P47), U1.39 (X2)
/P50: J1.20 (P50), U1.27 (~IRQ0)
/P51: J1.21 (P51), U1.28 (~IRQ1)
/P52: J1.22 (P52), U1.29 (~IRQ2)
/P53: J1.23 (P53), U1.30 (~RST)
/P54: J2.29 (P54), U1.32 (~DTAK)
/P55: J2.28 (P55), U1.31 (BSAV)
GND: C1.2, C2.2, EA1.1 (A), EA2.1 (A), J1.1 (GND), J2.48 (GND), R1.2, U1.21 (VSS), U2.3 (VSS)
unnamed: D1.1 (K), R1.1
unnamed: J2.26 (P57), U2.1 (SCIO)
VCC: C1.1, C2.1, D1.2 (A), J1.24 (VCC), J2.25 (VCC), U1.41 (VDD), U2.2 (VCC)
